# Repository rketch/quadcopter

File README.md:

# When Pigs Fly: The Quadcopter Project
The hardware and firmware for a quadcopter were made in the UCSD class CSE 176e: Robotic System Design and Implementation with [@ThomasStuart](https://github.com/ThomasStuart)

## Video of the quadcopter (click on gif)

## Report on the design process

## Various Pictures

Assembled quadcopter

Four bladed propellers with IMU breakout board

Remote PID control system tuning menu

Remote trim tuning menu

Quadcopter orientation angles

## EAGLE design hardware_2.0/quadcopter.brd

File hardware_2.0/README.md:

# EAGLE schematic and Board Files
These were updated in version 2.0 to fix wiring issues from the rainbow LED FETs to the microcontroller pins.

Created by  and  with continued updates and revisions by .

Libraries created by .

## Schematic

## Layout

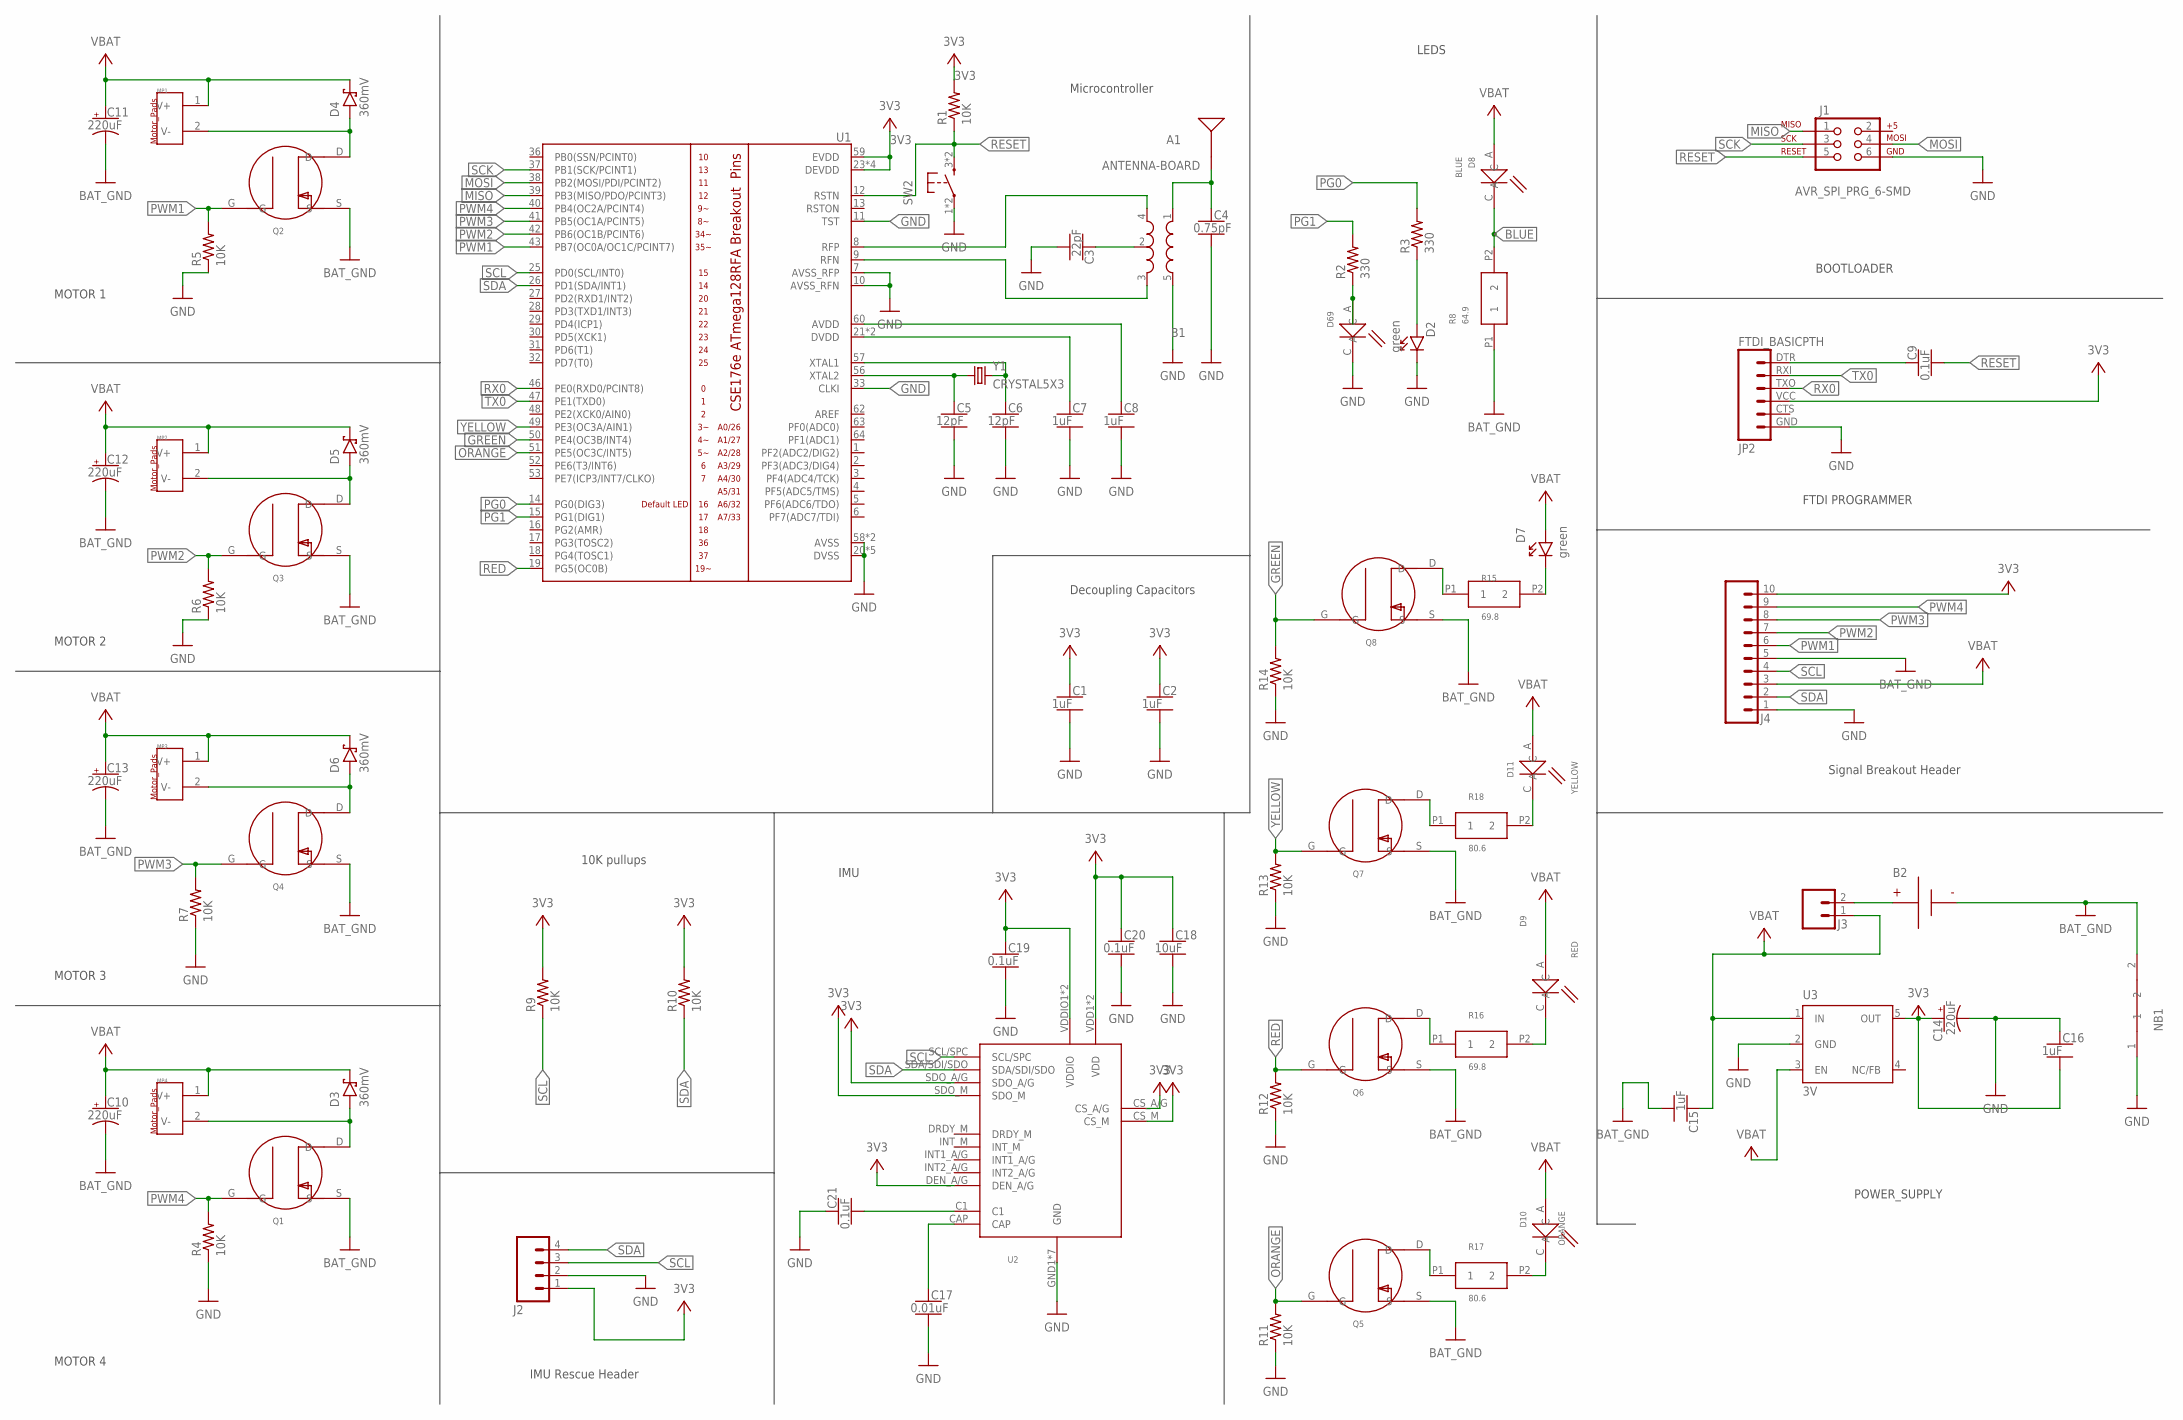
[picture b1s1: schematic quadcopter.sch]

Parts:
A1: ANTENNA-BOARD; ANT_PCB_2.4GHZ_NRF8001_1.6MM_1OZ
B1: BALUN0805; BALUN
B2: BATTERY-SCREW-TERMINAL; SCREW-TERMINAL-1X2-2.54MM
C1, C2, C7, C8, C15, C16: 1uF; CAPC2012X140_HS
C3: 22pF; CAPC2012X140_HS
C4: 0.75pF; CAPC2012X140_HS
C5, C6: 12pF; CAPC2012X140_HS
C9, C19, C20, C21: 0.1uF; CAPC2012X140_HS
C10, C11, C12, C13, C14: 220uF; CAPMP7343X310_HS
C17: 0.01uF; CAPC2012X140_HS
C18: 10uF; CAPC2012X140_HS
D2, D7: green; LEDSC125X200X120-2_HS
D3, D4, D5, D6: 360mV; SOD3716X135_HS
D8: BLUE; 0805_LED
D9: RED; 0805_LED
D10: ORANGE; 0805_LED
D11: YELLOW; 0805_LED
D69: LEDRED; 0805_LED
J1: AVR_SPI_PRG_6-SMD; 2X3-SMD
J2: HEADER-4POS-0.1IN-FEMALE; HDRVR4W80P254_1X4_1066X254X850B
J3: HEADER-0.1IN-2POS-MALE; HDRV2W63P254_2X1_508X254H838_HS
J4: HEADER-10POSTH-254X10; HDRV10W63P254_10X1_2540X254H838_HS
JP2: FTDI_BASICPTH; FTDI_BASIC
MP1, MP2, MP3, MP4: MOTOR_PADS-MOLEX-0530470210; MOLEX-0530470210
NB1: NETBRIDGE; NET_BRIDGE
Q1, Q2, Q3, Q4, Q5, Q6, Q7, Q8: NMOSFET-NMOSFET; N-CH_MOSFET
R1, R4, R5, R6, R7, R9, R10, R11, R12, R13, R14: 10K; RESC2012X60_HS
R2, R3: 330; RESC2012X60_HS
R8: 64.9; 0805_RESISTOR
R15, R16: 69.8; 0805_RESISTOR
R17, R18: 80.6; 0805_RESISTOR
SW2: PUSHBUTTON_-4.5X4.5; 4.5MM_TACTILE_SWITCH_TL3305AF160QG
U1: ATMEGA128RFA1; QFN-64
U2: LSM9DS1TR9AXISIMU-ACCEL/GYRO/MAGI2C/SPI24LGA; LSM9DS1TR9-AXISIMU
U3: 3V; SOT23-DBV
Y1: CRYSTAL5X3; CRYSTAL-SMD-5X3

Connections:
3V3: C1.1, C2.1, C14.1 (+), C16.2, C18.1, C19.1, C20.1, J2.1, J4.10, JP2.VCC (4), R1.2, R9.2, R10.2, U1.23 (DEVDD), U1.34 (DEVDD), U1.44 (DEVDD), U1.54 (DEVDD), U1.59 (EVDD), U2.CS_A/G, U2.CS_M, U2.DEN_A/G, U2.SDO_A/G, U2.SDO_M, U2.VDD1 (VDD), U2.VDD2 (VDD), U2.VDDIO1 (VDDIO), U2.VDDIO2 (VDDIO), U3.5 (OUT)
A2: B1.4 (OUT1), U1.8 (RFP)
A3: B1.2 (GND), C3.1
A4: B1.3 (OUT2), U1.9 (RFN)
ANT1: A1.FEED, B1.1 (IN), C4.1
BAT_GND: B2.1 (N), C10.2 (-), C11.2 (-), C12.2 (-), C13.2 (-), C15.2, J4.5, NB1.2, Q1.S, Q2.S, Q3.S, Q4.S, Q5.S, Q6.S, Q7.S, Q8.S, R8.P1 (1)
BLUE: D8.C, R8.P2 (2)
GND: B1.5 (GND), C1.2, C2.2, C3.2, C4.2, C5.2, C6.2, C7.2, C8.2, C14.2 (-), C16.1, C17.2, C18.2, C19.2, C20.2, C21.1, D2.C, D69.C, J1.6, J2.2, J4.1, JP2.GND (6), NB1.1, R4.1, R5.1, R6.1, R7.1, R11.1, R12.1, R13.1, R14.1, SW2.1, SW2.2 (1), U1.7 (AVSS_RFP), U1.10 (AVSS_RFN), U1.11 (TST), U1.20 (DVSS), U1.24 (DVSS), U1.33 (CLKI), U1.35 (DVSS), U1.45 (DVSS), U1.55 (DVSS), U1.58 (AVSS), U1.61 (AVSS), U2.GND1 (GND), U2.GND2 (GND), U2.RES1 (GND), U2.RES2 (GND), U2.RES3 (GND), U2.RES4 (GND), U2.RES5 (GND), U3.2 (GND)
GREEN: Q8.G, R14.2, U1.50 (PE4(OC3B/INT4))
MISO: J1.1, U1.39 (PB3(MISO/PDO/PCINT3))
MOSI: J1.4, U1.38 (PB2(MOSI/PDI/PCINT2))
unnamed: C5.1, U1.56 (XTAL2), Y1.1
unnamed: C6.1, U1.57 (XTAL1), Y1.3 (2)
unnamed: D2.A, R3.1
unnamed: B2.2, J3.2
unnamed: C7.1, U1.21 (DVDD), U1.22 (DVDD)
unnamed: C8.1, U1.60 (AVDD)
unnamed: D7.C, R15.P2 (2)
unnamed: Q8.D, R15.P1 (1)
unnamed: Q7.D, R18.P1 (1)
unnamed: D9.C, R16.P2 (2)
unnamed: Q6.D, R16.P1 (1)
unnamed: D10.C, R17.P2 (2)
unnamed: D11.C, R18.P2 (2)
unnamed: Q5.D, R17.P1 (1)
unnamed: D69.A, R2.1
unnamed: C9.1, JP2.DTR (1)
unnamed: D3.A, MP4.2 (V-), Q1.D
unnamed: D4.A, MP1.2 (V-), Q2.D
unnamed: D5.A, MP2.2 (V-), Q3.D
unnamed: C17.1, U2.CAP
unnamed: D6.A, MP3.2 (V-), Q4.D
unnamed: C21.2, U2.C1
ORANGE: Q5.G, R11.2, U1.51 (PE5(OC3C/INT5))
PG0: R3.2, U1.14 (PG0(DIG3))
PG1: R2.2, U1.15 (PG1(DIG1))
PWM1: J4.6, Q2.G, R5.2, U1.43 (PB7(OC0A/OC1C/PCINT7))
PWM2: J4.7, Q3.G, R6.2, U1.42 (PB6(OC1B/PCINT6))
PWM3: J4.8, Q4.G, R7.2, U1.41 (PB5(OC1A/PCINT5))
PWM4: J4.9, Q1.G, R4.2, U1.40 (PB4(OC2A/PCINT4))
RED: Q6.G, R12.2, U1.19 (PG5(OC0B))
RESET: C9.2, J1.5, R1.1, SW2.3 (2), SW2.4 (2), U1.12 (RSTN)
RX0: JP2.TXO (3), U1.46 (PE0(RXD0/PCINT8))
SCK: J1.3, U1.37 (PB1(SCK/PCINT1))
SCL: J2.3, J4.4, R9.1, U1.25 (PD0(SCL/INT0)), U2.SCL/SPC
SDA: J2.4, J4.2, R10.1, U1.26 (PD1(SDA/INT1)), U2.SDA/SDI/SDO
TX0: JP2.RXI (2), U1.47 (PE1(TXD0))
VBAT: C10.1 (+), C11.1 (+), C12.1 (+), C13.1 (+), C15.1, D3.C, D4.C, D5.C, D6.C, D7.A, D8.A, D9.A, D10.A, D11.A, J3.1, J4.3, MP1.1 (V+), MP2.1 (V+), MP3.1 (V+), MP4.1 (V+), U3.1 (IN), U3.3 (EN)
YELLOW: Q7.G, R13.2, U1.49 (PE3(OC3A/AIN1))

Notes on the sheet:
POWER_SUPPLY
Signal Breakout Header
IMU
MOTOR 1
MOTOR 2
MOTOR 3
MOTOR 4
IMU Rescue Header
FTDI PROGRAMMER
BOOTLOADER
LEDS
Microcontroller
10K pullups
Decoupling Capacitors

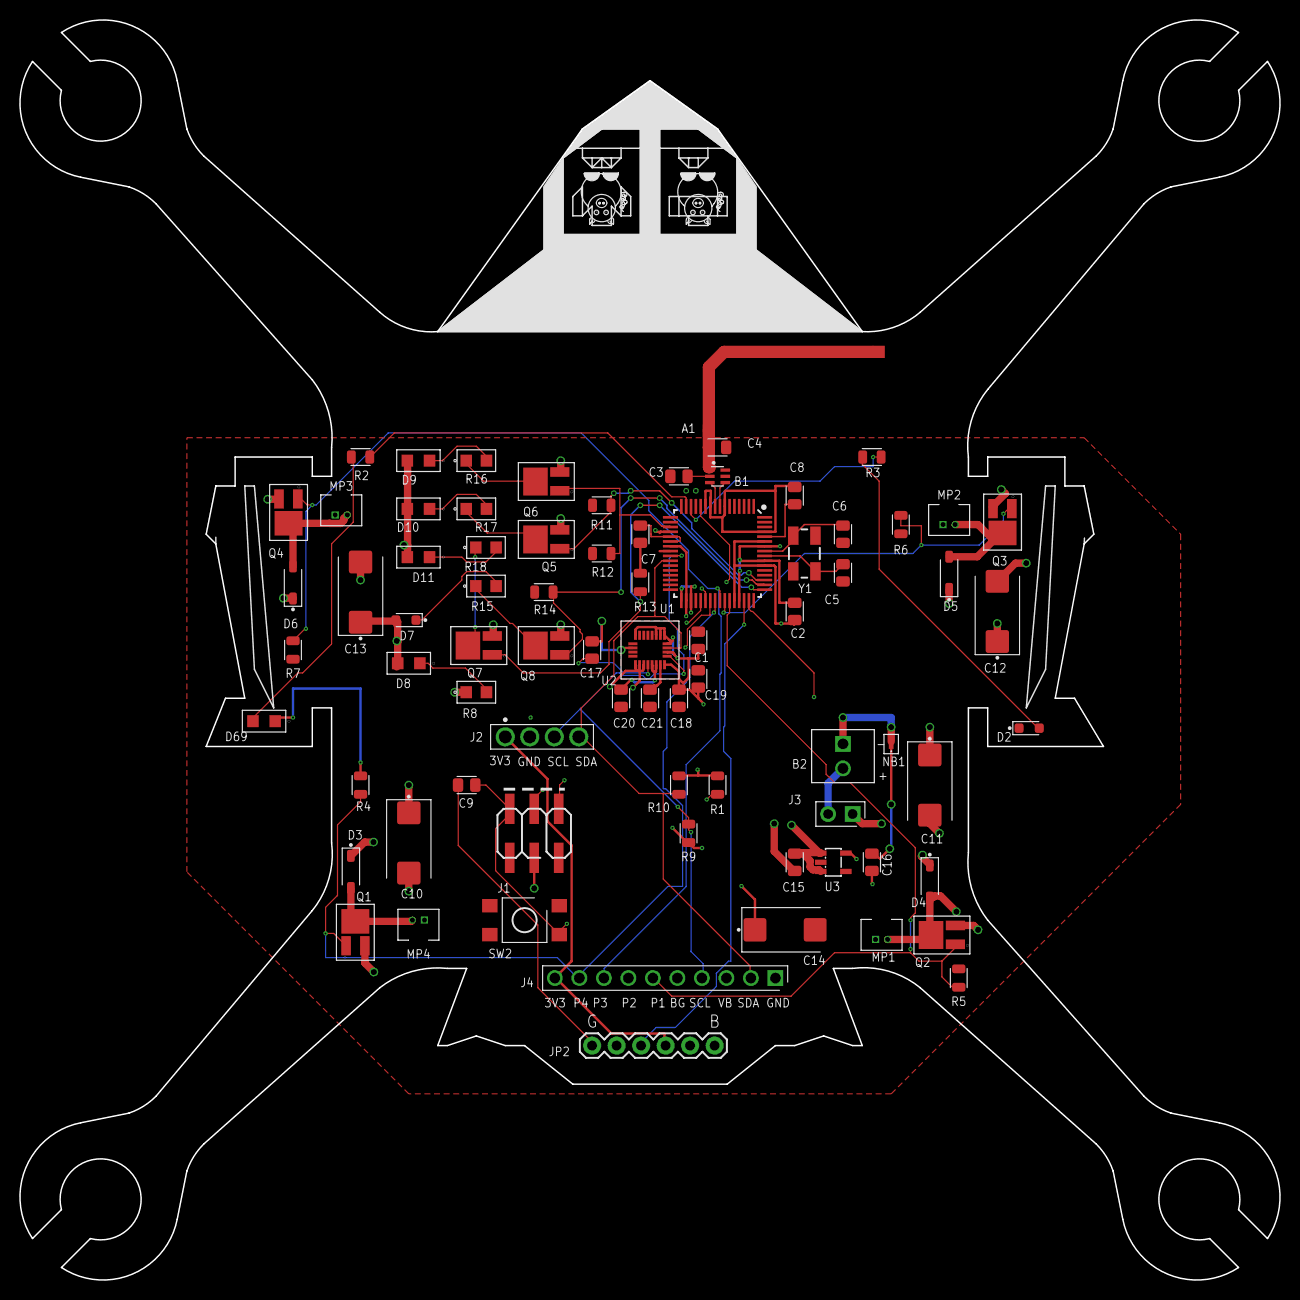
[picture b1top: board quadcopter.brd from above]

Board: 4 copper layers, 130.6 x 130.6 mm, 79 parts (0 on the bottom side), 49 nets.

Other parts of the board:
LABELS: LAYER_LABELS
PIG1, PIG2: PIG

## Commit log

2021-05-21 added readme
2021-05-26 doxygen support
2021-05-26 fix readme
2021-05-26 add images
2021-05-26 add photos to readme
2021-05-26 initial readme
2021-05-26 add BOM
2021-05-28 report
2021-05-28 fix port/starboard
2021-05-28 add pictures
2021-05-29 png to jpg
2021-05-29 add photo
2021-05-29 change name
2021-05-29 compress
2021-05-29 .gitignore and html/ folder
2021-05-29 change location of images file
2021-05-29 add doxygen
2021-05-29 update image
2021-07-21 Added Kalman Filter
